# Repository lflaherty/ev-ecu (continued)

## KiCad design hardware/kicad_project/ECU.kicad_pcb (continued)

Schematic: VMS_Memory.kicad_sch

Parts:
J3: Micro_SD_Card_Det; microSD_HC_Molex_104031-0811
R71, R72, R73, R74, R75, R99: 47k; R_0805_2012Metric
U16: CAT24C256YI-GT3; TSSOP-8_4.4x3mm_P0.65mm

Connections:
/VMS/MCU/EEPROM_ADDR0: U16.1 (A0); also elsewhere on the board
/VMS/MCU/EEPROM_ADDR1: U16.2 (A1); also elsewhere on the board
/VMS/MCU/EEPROM_ADDR2: U16.3 (A2); also elsewhere on the board
/VMS/MCU/EEPROM_WP: U16.7 (WP); also elsewhere on the board
/VMS/MCU/I2C0_SCL: U16.6 (SCL); also elsewhere on the board
/VMS/MCU/I2C0_SDA: U16.5 (SDA); also elsewhere on the board
/VMS/MCU/SDMMC_CLK: J3.5 (CLK); also elsewhere on the board
/VMS/MCU/SDMMC_CMD: J3.3 (CMD), R73.2; also elsewhere on the board
/VMS/MCU/SDMMC_DAT0: J3.7 (DAT0), R74.2; also elsewhere on the board
/VMS/MCU/SDMMC_DAT1: J3.8 (DAT1), R75.2; also elsewhere on the board
/VMS/MCU/SDMMC_DAT2: J3.1 (DAT2), R71.2; also elsewhere on the board
/VMS/MCU/SDMMC_DAT3: J3.2 (DAT3/CD), R72.2; also elsewhere on the board
/VMS/MCU/SDMMC_DET: J3.9 (DET_B), R99.2; also elsewhere on the board
GND: J3.6 (VSS), J3.11 (SHIELD), R99.1, U16.4 (GND); also elsewhere on the board

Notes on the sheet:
Author: LF
EEPROM (config data)
If DET switch open => SDMMC_DET pulled down If DET switch closed => SDMMC_DET tied high
SD card

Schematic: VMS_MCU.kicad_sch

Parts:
BT1: 3V/CR2032; BatteryHolder_Keystone_1060_1x2032
C31, C32: 2u2; C_0805_2012Metric
D14: LED; LED_0805_2012Metric
J4: ARM_SWD; PinHeader_2x05_P1.27mm_Vertical_SMD
R34, R35, R93, R94, R95, R96, R97: 2k2; R_0805_2012Metric
U3: STM32F765ZITx; LQFP-144_20x20mm_P0.5mm

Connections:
+3.3VA: U3.32 (VREF+), U3.33 (VDDA); also elsewhere on the board
+BATT: BT1.1 (+), U3.6 (VBAT); also elsewhere on the board
/SDC/ECU_ERR: U3.118 (PD4); also elsewhere on the board
/VMS/AIN/AIN_BUFF0: U3.44 (PC4); also elsewhere on the board
/VMS/AIN/AIN_BUFF1: U3.45 (PC5); also elsewhere on the board
/VMS/AIN/AIN_BUFF2: U3.46 (PB0); also elsewhere on the board
/VMS/AIN/AIN_BUFF3: U3.47 (PB1); also elsewhere on the board
/VMS/CAN/CAN0_RXD: U3.114 (PD0); also elsewhere on the board
/VMS/CAN/CAN0_TXD: U3.115 (PD1); also elsewhere on the board
/VMS/CAN/CAN1_RXD: U3.135 (PB5); also elsewhere on the board
/VMS/CAN/CAN1_TXD: U3.136 (PB6); also elsewhere on the board
/VMS/CAN/CAN2_RXD: U3.100 (PA8); also elsewhere on the board
/VMS/CAN/CAN2_TXD: U3.110 (PA15); also elsewhere on the board
/VMS/DIN/DIN0_3V3: U3.56 (PG0); also elsewhere on the board
/VMS/DIN/DIN1_3V3: U3.58 (PE7); also elsewhere on the board
/VMS/DIN/DIN2_3V3: U3.60 (PE9); also elsewhere on the board
/VMS/DIN/DIN3_3V3: U3.54 (PF14); also elsewhere on the board
/VMS/ExpansionHeaders/EXP_GPIO1: U3.68 (PE15); also elsewhere on the board
/VMS/ExpansionHeaders/EXP_I2C2_SCL: R35.2, U3.69 (PB10); also elsewhere on the board
/VMS/ExpansionHeaders/EXP_I2C2_SDA: R34.2, U3.70 (PB11); also elsewhere on the board
/VMS/ExpansionHeaders/EXP_SPI4_MISO: U3.66 (PE13); also elsewhere on the board
/VMS/ExpansionHeaders/EXP_SPI4_MOSI: U3.67 (PE14); also elsewhere on the board
/VMS/ExpansionHeaders/EXP_SPI4_SCK: U3.65 (PE12); also elsewhere on the board
/VMS/LEDDriver/START_L_ON: U3.50 (PF12); also elsewhere on the board
/VMS/MCU/BOOT0: U3.138 (BOOT0); also elsewhere on the board
/VMS/MCU/EEPROM_ADDR0: U3.91 (PG6); also elsewhere on the board
/VMS/MCU/EEPROM_ADDR1: U3.90 (PG5); also elsewhere on the board
/VMS/MCU/EEPROM_ADDR2: U3.89 (PG4); also elsewhere on the board
/VMS/MCU/EEPROM_WP: U3.92 (PG7); also elsewhere on the board
/VMS/MCU/GPS_3DFIX: U3.4 (PE5); also elsewhere on the board
/VMS/MCU/GPS_PPS: U3.5 (PE6); also elsewhere on the board
/VMS/MCU/GPS_RX: U3.129 (PG14); also elsewhere on the board
/VMS/MCU/GPS_TX: U3.97 (PC7); also elsewhere on the board
/VMS/MCU/HSE_IN: U3.23 (PH0); also elsewhere on the board
/VMS/MCU/HSE_OUT: U3.24 (PH1); also elsewhere on the board
/VMS/MCU/I2C0_SCL: R96.2, U3.11 (PF1); also elsewhere on the board
/VMS/MCU/I2C0_SDA: R97.2, U3.10 (PF0); also elsewhere on the board
/VMS/MCU/I2C1_SCL: R95.2, U3.81 (PD12); also elsewhere on the board
/VMS/MCU/I2C1_SDA: R94.2, U3.82 (PD13); also elsewhere on the board
/VMS/MCU/IMU_ADDR0: U3.86 (PD15); also elsewhere on the board
/VMS/MCU/IMU_INT: U3.85 (PD14); also elsewhere on the board
/VMS/MCU/LSE_IN: U3.8 (PC14); also elsewhere on the board
/VMS/MCU/LSE_OUT: U3.9 (PC15); also elsewhere on the board
/VMS/MCU/MPIO_EN1: U3.73 (PB12); also elsewhere on the board
/VMS/MCU/MPIO_EN2: U3.48 (PB2); also elsewhere on the board
/VMS/MCU/MPIO_EN3: U3.63 (PE10); also elsewhere on the board
/VMS/MCU/MPIO_EN4: U3.79 (PD10); also elsewhere on the board
/VMS/MCU/MPIO_EN5: U3.87 (PG2); also elsewhere on the board
/VMS/MCU/MPIO_EN6: U3.57 (PG1); also elsewhere on the board
/VMS/MCU/MPIO_EN7: U3.53 (PF13); also elsewhere on the board
/VMS/MCU/MPIO_EN8: U3.93 (PG8); also elsewhere on the board
/VMS/MCU/MPIO_IN1: U3.42 (PA6); also elsewhere on the board
/VMS/MCU/MPIO_IN2: U3.43 (PA7); also elsewhere on the board
/VMS/MCU/MPIO_IN3: U3.40 (PA4); also elsewhere on the board
/VMS/MCU/MPIO_IN4: U3.41 (PA5); also elsewhere on the board
/VMS/MCU/MPIO_IN5: U3.36 (PA2); also elsewhere on the board
/VMS/MCU/MPIO_IN6: U3.37 (PA3); also elsewhere on the board
/VMS/MCU/MPIO_IN7: U3.34 (PA0); also elsewhere on the board
/VMS/MCU/MPIO_IN8: U3.35 (PA1); also elsewhere on the board
/VMS/MCU/MPIO_OUT1: U3.74 (PB13); also elsewhere on the board
/VMS/MCU/MPIO_OUT2: U3.64 (PE11); also elsewhere on the board
/VMS/MCU/MPIO_OUT3: U3.59 (PE8); also elsewhere on the board
/VMS/MCU/MPIO_OUT4: U3.80 (PD11); also elsewhere on the board
/VMS/MCU/MPIO_OUT5: U3.88 (PG3); also elsewhere on the board
/VMS/MCU/MPIO_OUT6: U3.55 (PF15); also elsewhere on the board
/VMS/MCU/MPIO_OUT7: U3.49 (PF11); also elsewhere on the board
/VMS/MCU/MPIO_OUT8: U3.96 (PC6); also elsewhere on the board
/VMS/MCU/NRST: J4.10, U3.25 (NRST)
/VMS/MCU/P_SW1: U3.140 (PB9); also elsewhere on the board
/VMS/MCU/P_SW2: U3.141 (PE0); also elsewhere on the board
/VMS/MCU/P_SW3: U3.142 (PE1); also elsewhere on the board
/VMS/MCU/P_SW4: U3.1 (PE2); also elsewhere on the board
/VMS/MCU/P_SW5: U3.2 (PE3); also elsewhere on the board
/VMS/MCU/P_SW6: U3.3 (PE4); also elsewhere on the board
/VMS/MCU/SDC_BMS: U3.124 (PG9); also elsewhere on the board
/VMS/MCU/SDC_BSPD: U3.132 (PG15); also elsewhere on the board
/VMS/MCU/SDC_IMD: U3.125 (PG10); also elsewhere on the board
/VMS/MCU/SDC_OUT: U3.134 (PB4); also elsewhere on the board
/VMS/MCU/SDMMC_CLK: U3.113 (PC12); also elsewhere on the board
/VMS/MCU/SDMMC_CMD: U3.116 (PD2); also elsewhere on the board
/VMS/MCU/SDMMC_DAT0: U3.98 (PC8); also elsewhere on the board
/VMS/MCU/SDMMC_DAT1: U3.99 (PC9); also elsewhere on the board
/VMS/MCU/SDMMC_DAT2: U3.111 (PC10); also elsewhere on the board
/VMS/MCU/SDMMC_DAT3: U3.112 (PC11); also elsewhere on the board
/VMS/MCU/SDMMC_DET: U3.103 (PA11); also elsewhere on the board
/VMS/MCU/SWCLK: J4.4, U3.109 (PA14)
/VMS/MCU/SWDIO: J4.2, U3.105 (PA13)
/VMS/MCU/SWO: J4.6, U3.133 (PB3)
/VMS/MCU/USART_1_RX: U3.102 (PA10); also elsewhere on the board
/VMS/MCU/USART_1_TX: U3.101 (PA9); also elsewhere on the board
/VMS/MCU/USART_2_RX: U3.78 (PD9); also elsewhere on the board
/VMS/MCU/USART_2_TX: U3.77 (PD8); also elsewhere on the board
GND: BT1.2 (-), C31.2, C32.2, J4.3, J4.5, J4.9, R93.2, U3.16 (VSS), U3.31 (VSSA), U3.38 (VSS), U3.51 (VSS), U3.61 (VSS), U3.83 (VSS), U3.94 (VSS), U3.107 (VSS), U3.120 (VSS), U3.130 (VSS); also elsewhere on the board
unnamed: C31.1, U3.71 (VCAP_1)
unnamed: C32.1, U3.106 (VCAP_2)
unnamed: D14.1 (K), R93.1
unnamed: D14.2 (A), U3.104 (PA12)

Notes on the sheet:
Low ESR
Used for EEPROM
Used for IMU
Pinmap ADC1_IN0-ADC1_IN7
Author: LF

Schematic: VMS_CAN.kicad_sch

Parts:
R57, R58, R59: 120R; R_0805_2012Metric
U4, U5, U6: ISO1050DUB; SOP-8_6.62x9.15mm_P2.54mm

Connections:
+5V: U4.8 (VCC2), U5.8 (VCC2), U6.8 (VCC2); also elsewhere on the board
/VMS/CAN0_H: R57.2, U4.6 (CANL); also elsewhere on the board
/VMS/CAN0_L: R57.1, U4.7 (CANH); also elsewhere on the board
/VMS/CAN1_H: R58.2, U5.6 (CANL); also elsewhere on the board
/VMS/CAN1_L: R58.1, U5.7 (CANH); also elsewhere on the board
/VMS/CAN2_H: R59.2, U6.6 (CANL); also elsewhere on the board
/VMS/CAN2_L: R59.1, U6.7 (CANH); also elsewhere on the board
/VMS/CAN/CAN0_RXD: U4.2 (RXD); also elsewhere on the board
/VMS/CAN/CAN0_TXD: U4.3 (TXD); also elsewhere on the board
/VMS/CAN/CAN1_RXD: U5.2 (RXD); also elsewhere on the board
/VMS/CAN/CAN1_TXD: U5.3 (TXD); also elsewhere on the board
/VMS/CAN/CAN2_RXD: U6.2 (RXD); also elsewhere on the board
/VMS/CAN/CAN2_TXD: U6.3 (TXD); also elsewhere on the board
GND: U4.4 (GND1), U4.5 (GND2), U5.4 (GND1), U5.5 (GND2), U6.4 (GND1), U6.5 (GND2); also elsewhere on the board

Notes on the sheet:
Author: LF

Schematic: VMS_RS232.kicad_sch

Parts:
C1, C24, C25, C26, C27, C39: 100n; C_0805_2012Metric
U2: MAX3232IDWR; SOIC-16W_7.5x10.3mm_P1.27mm

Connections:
/VMS/ExpansionHeaders/RS232_2_RX: U2.8 (R2IN); also elsewhere on the board
/VMS/ExpansionHeaders/RS232_2_TX: U2.7 (T2OUT); also elsewhere on the board
/VMS/MCU/USART_1_RX: U2.12 (R1OUT); also elsewhere on the board
/VMS/MCU/USART_1_TX: U2.11 (T1IN); also elsewhere on the board
/VMS/MCU/USART_2_RX: U2.9 (R2OUT); also elsewhere on the board
/VMS/MCU/USART_2_TX: U2.10 (T2IN); also elsewhere on the board
/VMS/RS232_RX: U2.13 (R1IN); also elsewhere on the board
/VMS/RS232_TX: U2.14 (T1OUT); also elsewhere on the board
GND: C25.2, C27.1, C39.2, U2.15 (GND); also elsewhere on the board
unnamed: C1.1, U2.1 (C1+)
unnamed: C1.2, U2.3 (C1-)
unnamed: C24.1, U2.4 (C2+)
unnamed: C24.2, U2.5 (C2-)
unnamed: C25.1, U2.6 (VS-)
unnamed: C26.2, U2.2 (VS+)

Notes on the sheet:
Author: LF

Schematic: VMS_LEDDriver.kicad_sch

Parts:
Q1: PBHV8115T,215; SOT-23
R69, R70: 1k; R_0805_2012Metric

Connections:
/VMS/LEDDriver/START_L_ON: R69.2; also elsewhere on the board
/VMS/START_L: R70.1; also elsewhere on the board
GND: Q1.2 (E); also elsewhere on the board
unnamed: Q1.1 (B), R69.1
unnamed: Q1.3 (C), R70.2

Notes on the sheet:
STARTL_ON is a 3V3 signal from MCU STARTL is the output to be in series with the LED on dash
TODO * Resistor sizing * Test * Is this BJT part ok? Change to something JLC has?

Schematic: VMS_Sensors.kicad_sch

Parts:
C48: 100n; C_0805_2012Metric
C49, C50, C51: 2n2; C_0805_2012Metric
IC6: 790; Manufacturer_Part_Number 790; Mouser Part Number 485-790
J5: 619540-1; 6195401; Manufacturer_Part_Number 619540-1; Mouser Part Number 571-619540-1
U8: MPU-6050; InvenSense_QFN-24_4x4mm_P0.5mm

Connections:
+BATT: IC6.4 (VBACKUP); also elsewhere on the board
/VMS/MCU/GPS_3DFIX: IC6.5 (3D-FIX); also elsewhere on the board
/VMS/MCU/GPS_PPS: IC6.13 (1PPS); also elsewhere on the board
/VMS/MCU/GPS_RX: IC6.10 (RX); also elsewhere on the board
/VMS/MCU/GPS_TX: IC6.9 (TX); also elsewhere on the board
/VMS/MCU/I2C1_SCL: U8.23 (SCL); also elsewhere on the board
/VMS/MCU/I2C1_SDA: U8.24 (SDA); also elsewhere on the board
/VMS/MCU/IMU_ADDR0: U8.9 (AD0); also elsewhere on the board
/VMS/MCU/IMU_INT: U8.12 (INT); also elsewhere on the board
GND: C48.2, C49.2, C50.2, C51.2, IC6.3 (GND_1), IC6.8 (GND_2), IC6.12 (GND_3), IC6.19 (GND_4), J5.2, J5.3, J5.4, J5.5, U8.1 (CLKIN), U8.11 (FSYNC), U8.18 (GND); also elsewhere on the board
unnamed: C50.1, U8.10 (REGOUT)
unnamed: C51.1, U8.20 (CPOUT)
unnamed: IC6.11 (EX_ANT), J5.1

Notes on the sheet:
GPS
Author: LF
IMU

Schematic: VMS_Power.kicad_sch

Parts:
C79, C80: 10u; C_0805_2012Metric
C81: 100n; C_0805_2012Metric
C82: 10n; C_0805_2012Metric
D6: B5819W; D_SOD-123
D15: LED; LED_0805_2012Metric
FB1, FB2: 100 @ 100MHz; L_0805_2012Metric
R98: 2k2; R_0805_2012Metric
U12: ZLDO1117QG33TA; SOT-223-3_TabPin2

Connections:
+3.3VA: C81.1, C82.1, FB1.1; also elsewhere on the board
+5V: D6.2 (A); also elsewhere on the board
GND: C79.2, C80.2, C81.2, C82.2, R98.2, U12.1 (GND); also elsewhere on the board
unnamed: C79.1, FB2.1, U12.3 (VI)
unnamed: D6.1 (K), FB2.2
unnamed: D15.1 (K), R98.1

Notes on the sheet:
2022-10-16: Changed U12 from LM1117MPX-33NOPB (https://www.ti.com/lit/ds/symlink/lm1117.pdf) to ZLDO1117QG33TA as a equivalent part due to availablity issues.
Author: LF
3v3 regulator
Analog reference voltage

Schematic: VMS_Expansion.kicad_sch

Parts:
H1, H2, H3: MountingHole; MountingHole_2.5mm
J2: Expansion; PinHeader_2x09_P2.54mm_Vertical

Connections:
+5V: J2.3, J2.4; also elsewhere on the board
/VMS/BATT_SPARE_1: J2.17; also elsewhere on the board
/VMS/BATT_SPARE_2: J2.18; also elsewhere on the board
/VMS/ExpansionHeaders/EXP_GPIO1: J2.12; also elsewhere on the board
/VMS/ExpansionHeaders/EXP_I2C2_SCL: J2.9; also elsewhere on the board
/VMS/ExpansionHeaders/EXP_I2C2_SDA: J2.7; also elsewhere on the board
/VMS/ExpansionHeaders/EXP_SPI4_MISO: J2.13; also elsewhere on the board
/VMS/ExpansionHeaders/EXP_SPI4_MOSI: J2.11; also elsewhere on the board
/VMS/ExpansionHeaders/EXP_SPI4_SCK: J2.15; also elsewhere on the board
/VMS/ExpansionHeaders/RS232_2_RX: J2.8; also elsewhere on the board
/VMS/ExpansionHeaders/RS232_2_TX: J2.10; also elsewhere on the board
/VMS/HEADER_SPARE_1: J2.16; also elsewhere on the board
/VMS/VMS_PROG: J2.14; also elsewhere on the board
GND: J2.1, J2.2; also elsewhere on the board

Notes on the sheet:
Author: LF

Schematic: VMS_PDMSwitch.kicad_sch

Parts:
Q2, Q3, Q4, Q5, Q6, Q7: PBHV8115T,215; SOT-23
R17, R18, R30, R31, R32, R33: 1k; R_0805_2012Metric

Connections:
/POWER/P_SW1: Q2.2 (E); also elsewhere on the board
/POWER/P_SW2: Q3.2 (E); also elsewhere on the board
/POWER/P_SW3: Q4.2 (E); also elsewhere on the board
/POWER/P_SW4: Q5.2 (E); also elsewhere on the board
/POWER/P_SW5: Q6.2 (E); also elsewhere on the board
/POWER/P_SW6: Q7.2 (E); also elsewhere on the board
/VMS/MCU/P_SW1: R17.2; also elsewhere on the board
/VMS/MCU/P_SW2: R18.2; also elsewhere on the board
/VMS/MCU/P_SW3: R30.2; also elsewhere on the board
/VMS/MCU/P_SW4: R31.2; also elsewhere on the board
/VMS/MCU/P_SW5: R32.2; also elsewhere on the board
/VMS/MCU/P_SW6: R33.2; also elsewhere on the board
unnamed: Q2.1 (B), R17.1
unnamed: Q3.1 (B), R18.1
unnamed: Q4.1 (B), R30.1
unnamed: Q5.1 (B), R31.1
unnamed: Q6.1 (B), R32.1
unnamed: Q7.1 (B), R33.1

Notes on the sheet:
Author: LF
Resistor connected in power schem

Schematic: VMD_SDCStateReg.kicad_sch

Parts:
R28, R36, R40: 4k7; R_0805_2012Metric
R29, R37, R39, R41: 1k; R_0805_2012Metric
R38: 470R; R_0805_2012Metric
ZD5, ZD10, ZD17, ZD18: 3.3V; D_MiniMELF

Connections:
/BSPD/BSPD_ERR: R38.1; also elsewhere on the board
/SDC/BMS_ERR: R28.1; also elsewhere on the board
/SDC/IMD_ERR: R36.1; also elsewhere on the board
/SDC/SDC_OUT: R40.1; also elsewhere on the board
/VMS/MCU/SDC_BMS: R28.2, R29.1, ZD5.1 (K); also elsewhere on the board
/VMS/MCU/SDC_BSPD: R38.2, R39.1, ZD17.1 (K); also elsewhere on the board
/VMS/MCU/SDC_IMD: R36.2, R37.1, ZD10.1 (K); also elsewhere on the board
/VMS/MCU/SDC_OUT: R40.2, R41.1, ZD18.1 (K); also elsewhere on the board
GND: R29.2, R37.2, R39.2, R41.2, ZD5.2 (A), ZD10.2 (A), ZD17.2 (A), ZD18.2 (A); also elsewhere on the board

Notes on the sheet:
Author: LF
SDC 0-5V/0-24V digital to 0-3.3V

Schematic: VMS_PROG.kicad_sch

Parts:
C2: 100n; C_0805_2012Metric
R43: 10k; R_0805_2012Metric
R44: 220R; R_0805_2012Metric
U9: 74HC14D,653; SOIC-14_3.9x8.7mm_P1.27mm

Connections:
/VMS/MCU/BOOT0_EXT: R44.2; also elsewhere on the board
/VMS/VMS_PROG: R43.2, U9.1; also elsewhere on the board
GND: C2.2, U9.3, U9.5, U9.7 (GND), U9.9, U9.11, U9.13; also elsewhere on the board
unnamed: R44.1, U9.2

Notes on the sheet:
Author: LF
Leave VMS_PROG open for BOOT0=0V (normal boot mode) Tie VMS_PROG to GND for BOOT0=3.3V (flash update mode)
When VMS_PROG pulled down, R43 330uA/1mW.

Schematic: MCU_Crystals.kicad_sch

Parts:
C33, C34, C52, C53: 12p; C_0805_2012Metric
R87: 220R; R_0805_2012Metric
Y1: 16MHz; Crystal_SMD_3225-4Pin_3.2x2.5mm
Y2: 32.768kHz (ECS-.327-9-34QN-TR); Crystal_SMD_3215-2Pin_3.2x1.5mm

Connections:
/VMS/MCU/HSE_IN: C33.1, Y1.1; also elsewhere on the board
/VMS/MCU/HSE_OUT: R87.1; also elsewhere on the board
/VMS/MCU/LSE_IN: C52.1, Y2.1; also elsewhere on the board
/VMS/MCU/LSE_OUT: C53.1, Y2.2; also elsewhere on the board
GND: C33.2, C34.2, C52.2, C53.2, Y1.2, Y1.4; also elsewhere on the board
unnamed: C34.1, R87.2, Y1.3

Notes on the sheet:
Author: LF
C_Load = 2*(C_LOAD_CRYSTAL - C_PARASITIC) = 2 * (9pF - 2pF (or less)) = 14pF (or less)

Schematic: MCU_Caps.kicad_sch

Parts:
C3, C11, C12, C13, C14, C19, C20, C21, C22, C23, C55, C56, C57, C58, C59, C60, C61, C62, C63, C64, C65, C66: 100n; C_0805_2012Metric
C4: 4u7; C_0805_2012Metric
C15, C54: 1u; C_0805_2012Metric

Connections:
GND: C3.2, C4.2, C11.2, C12.2, C13.2, C14.2, C15.2, C19.2, C20.2, C21.2, C22.2, C23.2, C54.2, C55.2, C56.2, C57.2, C58.2, C59.2, C60.2, C61.2, C62.2, C63.2, C64.2, C65.2, C66.2; also elsewhere on the board

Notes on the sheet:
Pin 62
Pin 17
Pin 72
Pin 52
Pin 131
VDDUSB
Pin 144
Pin 108
Pin 30
Decoupling cap close to pkg
VDDSDMMC
Ceramic bypass caps
Author: LF
Pin 39
Pin 84

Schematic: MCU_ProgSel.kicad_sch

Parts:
JP1: BOOT_EXT; SolderJumper-2_P1.3mm_Open_RoundedPad1.0x1.5mm
JP6: BOOT; SolderJumper-3_P1.3mm_Open_RoundedPad1.0x1.5mm_NumberLabels
R100, R101: 10k; R_0805_2012Metric

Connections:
/VMS/MCU/BOOT0: JP1.1 (A), JP6.2 (C); also elsewhere on the board
/VMS/MCU/BOOT0_EXT: JP1.2 (B); also elsewhere on the board
GND: R101.2; also elsewhere on the board
unnamed: JP6.1 (A), R100.2
unnamed: JP6.3 (B), R101.1

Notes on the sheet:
Tie BOOT0 to 3.3v to program. 0V to boot from internal flash. Switch between hardwired and configurable.
BOOT0 (PROG) pin selection
Author: LF

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
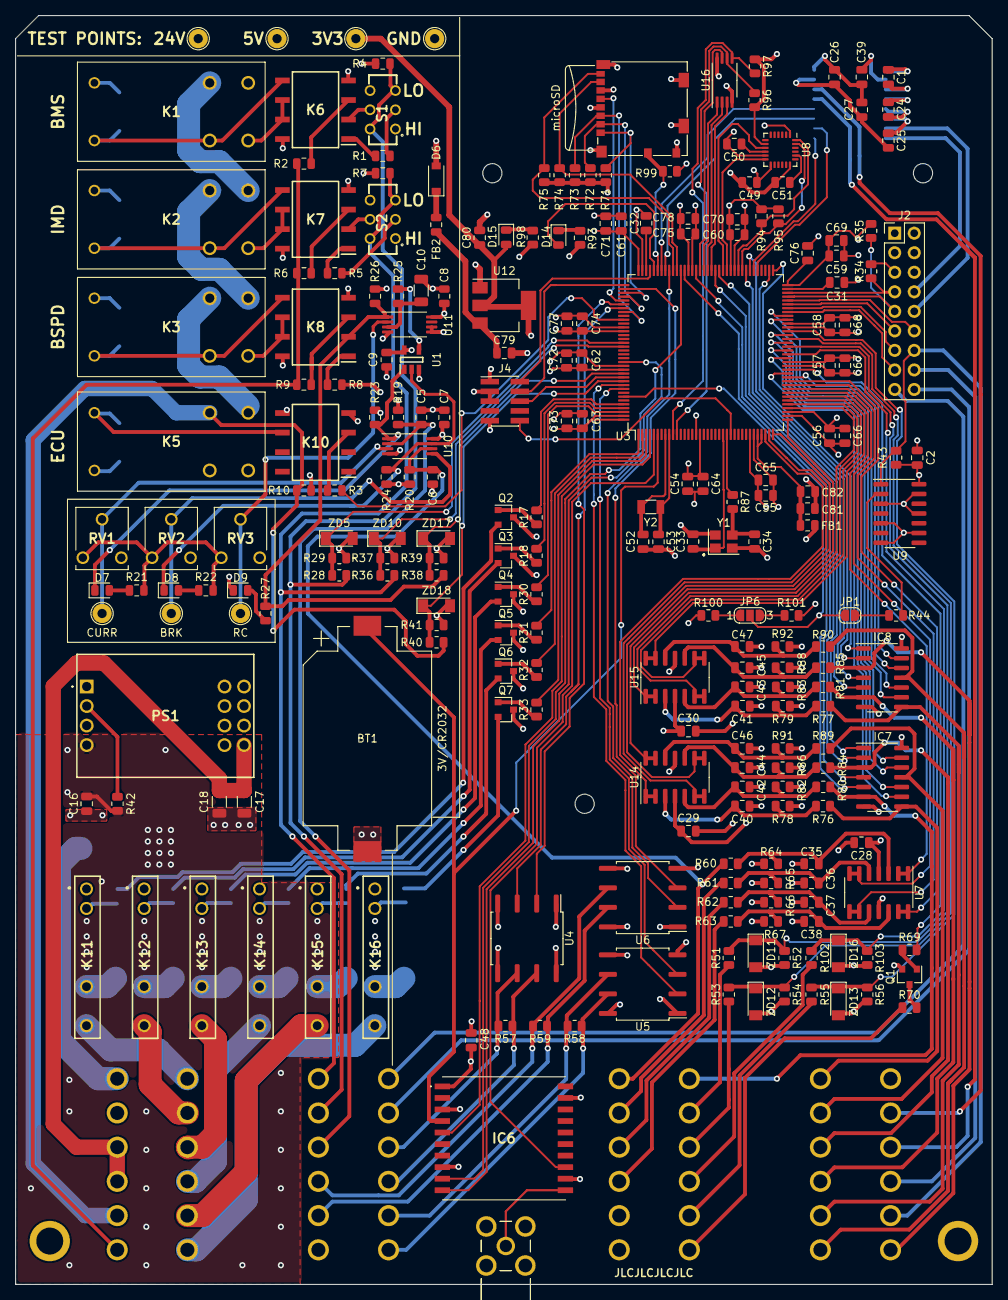
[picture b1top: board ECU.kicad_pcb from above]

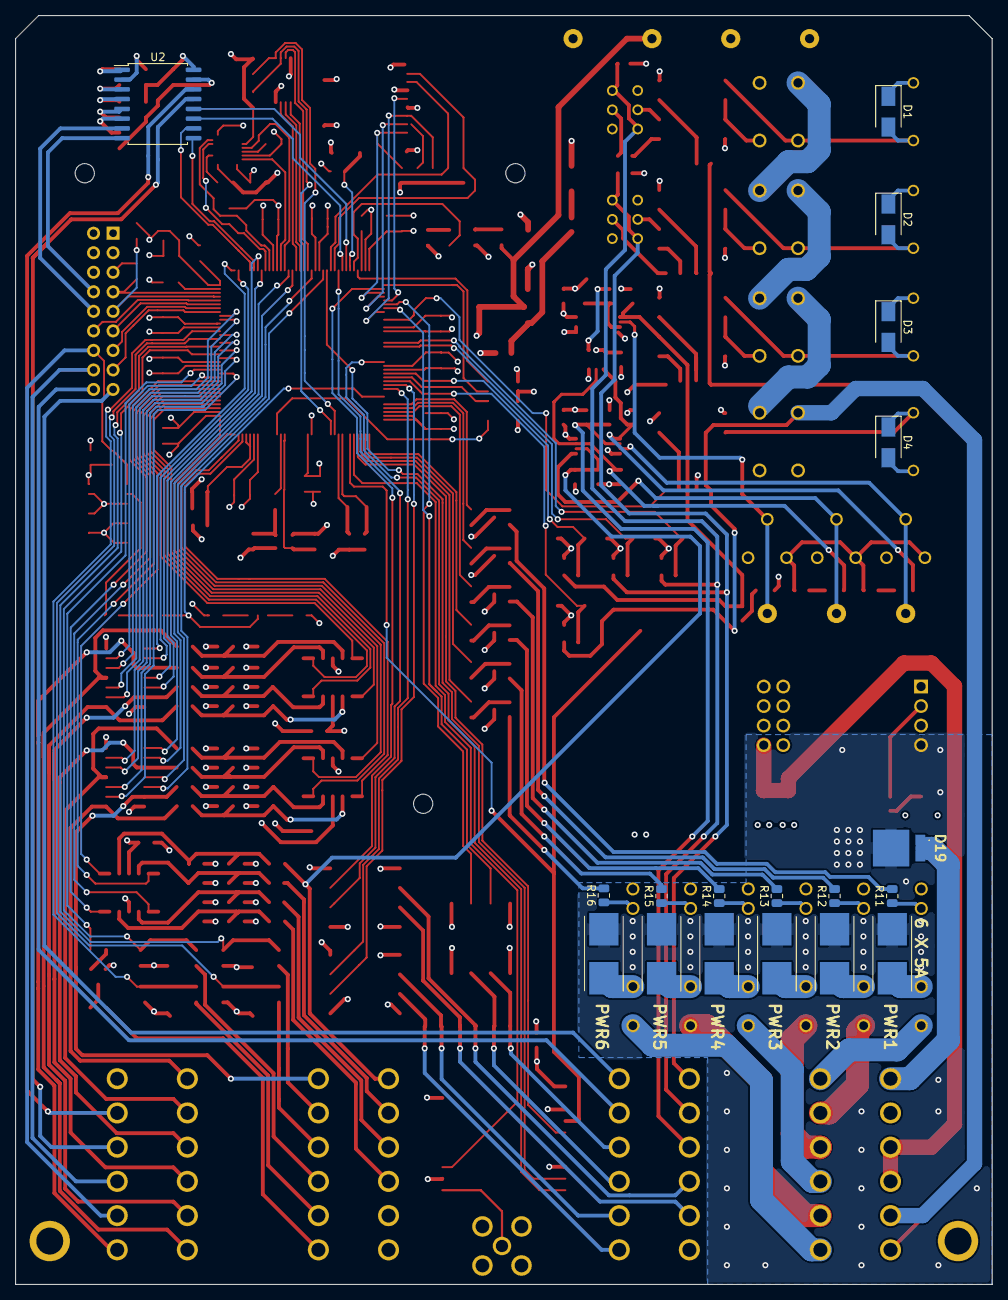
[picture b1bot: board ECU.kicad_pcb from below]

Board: 4 copper layers, 127.0 x 165.0 mm, 258 parts (18 on the bottom side), 231 nets.

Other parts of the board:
C67, C68, C69, C70, C71, C72, C73, C77, C78: 100n; C_0805_2012Metric
C74, C75: 1u; C_0805_2012Metric
C76: 4u7; C_0805_2012Metric

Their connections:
GND: C67.2, C68.2, C69.2, C70.2, C71.2, C72.2, C73.2, C74.2, C75.2, C76.2, C77.2, C78.2; also elsewhere on the board

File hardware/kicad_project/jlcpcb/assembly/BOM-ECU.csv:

Comment,Designator,Footprint,LCSC
100 @ 100MHz,"FB1,FB2",L_0805_2012Metric,C1015
16MHz,Y1,Crystal_SMD_3225-4Pin_3.2x2.5mm,C13738
100k,R42,R_0805_2012Metric,C149504
100u,C10,C_1206_3216Metric,C15008
10u/35V,"C16,C79,C80",C_0805_2012Metric,C15850
10n,C82,C_0805_2012Metric,C1710
10k,"R100,R101,R26,R4,R43,R7",R_0805_2012Metric,C17414
120R,"R57,R58,R59",R_0805_2012Metric,C17437
12k,"R64,R65,R66,R67,R78,R79,R82,R83,R86,R88,R91,R92",R_0805_2012Metric,C17444
1k,"R1,R10,R103,R17,R18,R2,R21,R22,R29,R30,R31,R32,R33,R37,R39,R41,R5,R52,R54,R56,R6,R69,R70,R8,R9",R_0805_2012Metric,C17513
2k2,"R34,R35,R93,R94,R95,R96,R97,R98",R_0805_2012Metric,C17520
220R,"R44,R87",R_0805_2012Metric,C17557
4k7,"R102,R19,R20,R23,R24,R25,R27,R28,R36,R40,R51,R53,R55",R_0805_2012Metric,C17673
470R,R38,R_0805_2012Metric,C17710
47k,"R71,R72,R73,R74,R75,R99",R_0805_2012Metric,C17713
6k2,"R60,R61,R62,R63,R76,R77,R80,R81,R84,R85,R89,R90",R_0805_2012Metric,C17767
4u7,C76,C_0805_2012Metric,C1779
680R,R3,R_0805_2012Metric,C17798
12p,"C33,C34,C52,C53",C_0805_2012Metric,C1792
"PBHV8115T,215","Q1,Q2,Q3,Q4,Q5,Q6,Q7",SOT-23,C282549
2n2,"C49,C50,C51",C_0805_2012Metric,C28260
1u,"C7,C74,C75,C8,C9",C_0805_2012Metric,C28323
32.768kHz (ECS-.327-9-34QN-TR),Y2,Crystal_SMD_3215-2Pin_3.2x1.5mm,C32346
1n2,"C35,C36,C37,C38,C40,C41,C42,C43,C44,C45,C46,C47",C_0805_2012Metric,C46653
2u2,"C31,C32",C_0805_2012Metric,C49217
100n,"C1,C2,C24,C25,C26,C27,C28,C29,C30,C39,C48,C5,C54,C55,C56,C57,C58,C59,C6,C60,C61,C62,C63,C64,C65,C66,C67,C68,C69,C70,C71,C72,C73,C77,C78,C81",C_0805_2012Metric,C49678
"74HC14D,653",U9,SOIC-14_3.9x8.7mm_P1.27mm,C5605
22u,"C17,C18",C_1206_3216Metric,C5672
LM324DT,"U14,U15,U7",SOIC-14_3.9x8.7mm_P1.27mm,C71035
3.3V,"ZD10,ZD11,ZD12,ZD13,ZD16,ZD17,ZD18,ZD5",D_MiniMELF,C8056
LED,"D14,D15,D7,D8,D9",LED_0805_2012Metric,C84256
B5819W,D6,D_SOD-123,C8598
